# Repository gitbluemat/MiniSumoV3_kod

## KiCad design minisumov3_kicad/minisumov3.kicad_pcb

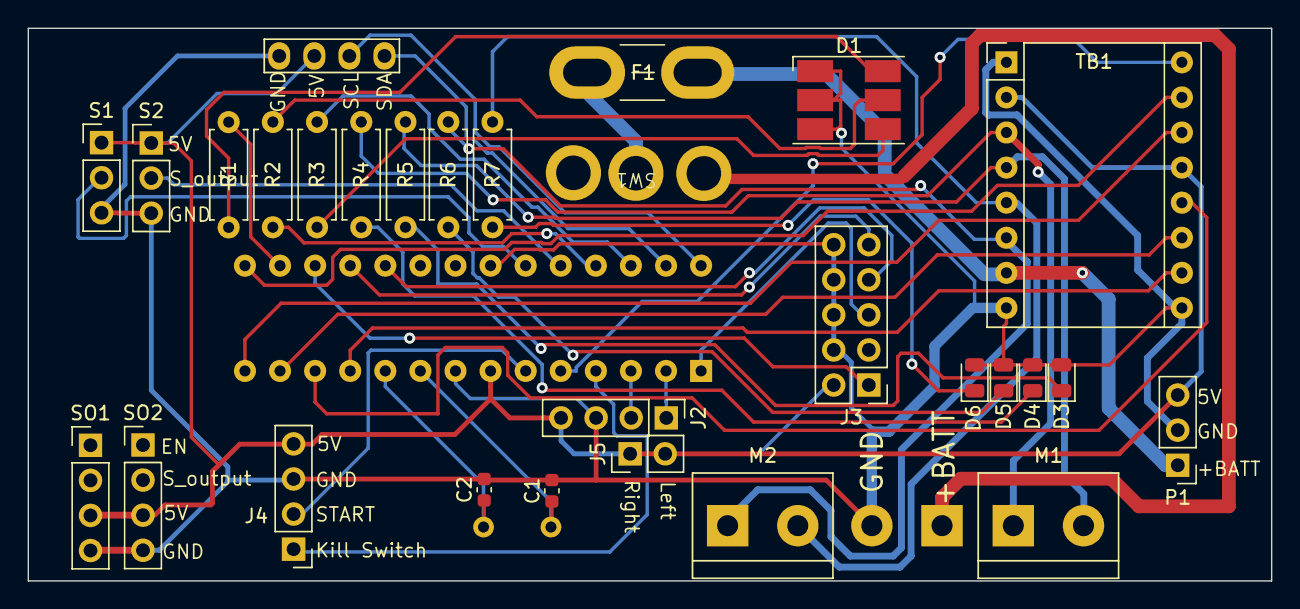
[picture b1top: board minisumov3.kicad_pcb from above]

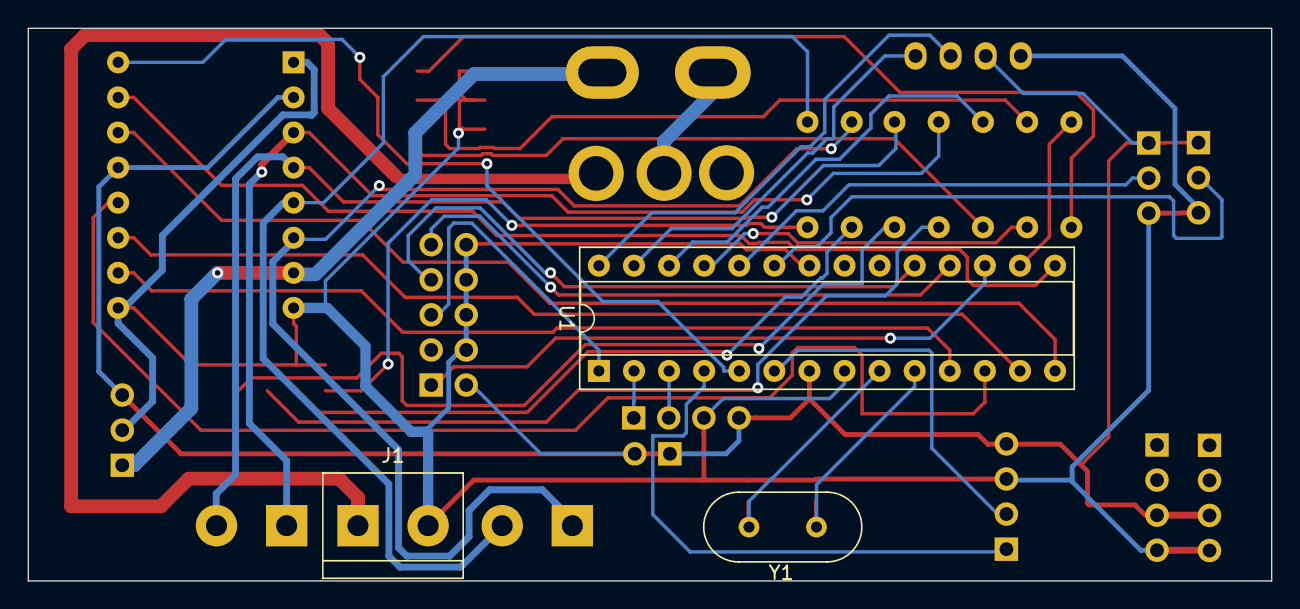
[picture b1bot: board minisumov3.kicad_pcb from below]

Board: 2 copper layers, 90.0 x 40.0 mm, 32 parts (3 on the bottom side), 39 nets.

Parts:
Brd1: SSD1306; 128x64OLED
C1, C2: 22pF; C_0603_1608Metric
D1: LED_RGB; LED_RGB_Cree-PLCC-6_6x5mm_P2.1mm
D3, D4, D5, D6: LED; LED_0805_2012Metric
F1: ~2.5A; Fuse_Blade_Mini_directSolder
J1: POWER_CONN; TerminalBlock_bornier-2_P5.08mm
J2: uart1; PinHeader_1x04_P2.54mm_Vertical
J3: AVR-ISP-10; PinHeader_2x05_P2.54mm_Vertical
J4: startmodule; PinHeader_1x04_P2.54mm_Vertical
J5: change_direction; PinHeader_1x02_P2.54mm_Vertical
M1, M2: Motor_DC; TerminalBlock_bornier-2_P5.08mm
P1: pololu2119; PinHeader_1x03_P2.54mm_Vertical
R1, R2, R3: 220; R_Axial_DIN0207_L6.3mm_D2.5mm_P7.62mm_Horizontal
R4, R5, R6, R7: 330; R_Axial_DIN0207_L6.3mm_D2.5mm_P7.62mm_Horizontal
S1, S2: QTR-1A; PinHeader_1x03_P2.54mm_Vertical
SO1, SO2: pololu 2578; PinHeader_1x04_P2.54mm_Vertical
SW1: SW_DIP_x01; On-On-Switch
TB1: POLOLU-713; Pololu_Breakout-16_15.2x20.3mm
U1: ATmega328-P; DIP-28_W7.62mm_Socket
Y1: Crystal; Crystal_HC49-4H_Vertical

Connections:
+5V: Brd1.2 (VCC), J2.4, J3.2 (VCC), J4.4, J5.1, J5.2, P1.3 (VOUT), S1.1 (VIN), S2.1 (VIN), SO1.3 (VDD), SO2.3 (VDD), TB1.2 (VCC), TB1.13 (~STBY), U1.7 (VCC)
+BATT: F1.2, P1.1 (VIN), TB1.7 (VMOT)
AIN1: TB1.14 (AIN1), U1.14 (PB0)
AIN2: TB1.15 (AIN2), U1.15 (PB1)
AO1: M1.1 (+), R4.2, TB1.3 (AO1)
AO2: M1.2 (-), R5.2, TB1.4 (AO2)
BIN1: TB1.12 (BIN1), U1.12 (PD6)
BIN2: TB1.11 (BIN2), U1.13 (PD7)
BO1: M2.1 (+), R6.2, TB1.6 (BO1)
BO2: M2.2 (-), R7.2, TB1.5 (BO2)
Blue: R3.2, U1.26 (PC3)
GND: Brd1.1 (GND), C1.2, C2.2, D1.1 (RK), D1.2 (GK), D1.3 (BK), D3.2 (A), D4.2 (A), D5.2 (A), D6.2 (A), J1.2, J2.3, J3.4 (GND), J3.6 (GND), J3.8 (GND), J3.10 (GND), J4.3, P1.2 (GND), S1.3 (GND), S2.3 (GND), SO1.4 (GND), SO2.4 (GND), TB1.1 (GND), TB1.8 (GND), TB1.9 (GND), U1.8 (GND), U1.22 (GND)
Green: R2.2, U1.25 (PC2)
KS: J4.1, U1.4 (PD2)
MISO: J3.9 (MISO), U1.18 (PB4)
MOSI: J3.1 (MOSI), U1.17 (PB3)
unnamed: D1.4 (BA), R3.1
unnamed: D1.5 (GA), R2.1
unnamed: D1.6 (RA), R1.1
unnamed: D3.1 (K), R5.1
unnamed: D4.1 (K), R4.1
unnamed: D5.1 (K), R6.1
unnamed: D6.1 (K), R7.1
unnamed: F1.1, SW1.2
unnamed: J1.1, SW1.1
unnamed: J2.1, U1.2 (PD0)
unnamed: J2.2, U1.3 (PD1)
unnamed: C1.1, U1.9 (XTAL1/PB6), Y1.2
unnamed: C2.1, U1.10 (XTAL2/PB7), Y1.1
PWMA: TB1.16 (PWMA), U1.5 (PD3)
PWMB: TB1.10 (PWMB), U1.11 (PD5)
RST: J3.5 (~RST), U1.1 (~RESET/PC6)
Red: R1.2, U1.16 (PB2)
S1: S1.2 (OUT), U1.23 (PC0)
S2: S2.2 (OUT), U1.24 (PC1)
SCK: J3.7 (SCK), U1.19 (PB5)
SCL: Brd1.3 (SCL), U1.28 (PC5)
SDA: Brd1.4 (SDA), U1.27 (PC4)
START: J4.2, U1.6 (PD4)

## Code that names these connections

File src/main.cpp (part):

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#include "../QTRSensors/QTRSensors.h"

// POLOLU-713
#define AIN1  8
#define AIN2  9

#define BIN1 PD6
#define BIN2 PD7

#define PWMA PD3
#define PWMB PD5

// status LED
#define led_red PB2
#define led_green A2

// IR remote
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  pinMode(sensorPin1, INPUT);
  pinMode(sensorPin2, INPUT);

  pinMode(AIN1, OUTPUT);
  pinMode(AIN2, OUTPUT);
  pinMode(BIN1, OUTPUT);
  pinMode(BIN2, OUTPUT);
  pinMode(PWMA, OUTPUT);
  pinMode(PWMB, OUTPUT);

  pinMode(left_sensor, INPUT);
  pinMode(right_sensor, INPUT);
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
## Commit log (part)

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2026-01-24 wersja kodu przed dodaniem startu z psp (startmodule)
2026-01-24 dodano logi zmian
2026-01-24 plik zmian (log)
2026-01-24 wersja gotowa do startu z pilota nie kompletna (problemy z zegarem / podpieciem elektronicznym do sprawdzenia pozniej)
2026-02-06 dodano pliki do plytki z kicad
2026-06-06 Updated platformio.ini with additional board settings and dependencies; enhanced main.cpp with improved IR command handling and motor control functions; modified zmiany.log to include new timestamps.
